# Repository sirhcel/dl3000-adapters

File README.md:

# Banana Jack and BNC Adapters for RIGOL DL3000 Electronic Loads

## Overview

This project is about banana jack and BNC adapters for RIGOL's DL3000 series
electronic loads. There are already adapters for narrower binding posts (like
BK Precision, ...) but I did not find any for the 39 mm pitch of the RIGOL
DL3000 series.

These adapters are meant for conveniently feeding a few amperes - not for high
current applications.

## Variants and Bills of Material

### BNC Adapter

The BNC adapter has a pretty standard footprint. So you should be able to find
a suitable replacement from your preferred distributor. Information on
replacement parts welcome.

* 1 PCB
    * KiCad design files form this repository
    * [Gerber and drill files](orders/dl3000-bnc-adapter-1.0-85dbc15.zip)
    * [Or just order it from OSH Park](https://oshpark.com/shared\_projects/MOcX6Gow)
* 1 [BNC connector](https://www.reichelt.de/steckverbinder-bnc-75-ohm-gerade-rnd-205-00437-p194660.html)

### Banana Jack Adapters

There are two board variants for sourcing the connectors from different
distributors.

#### PB4 Banana Jack Adapter

* 1 PCB
    * KiCad design files from this repository
    * [Gerber an drill files](orders/dl3000-banana-adapter-1.0-85dbc15.zip)
    * [Or just order it from OSH Park](https://oshpark.com/shared\_projects/gLsNtQ88)
* 1 connector Hirschmann Test and Measurement
  [PB4 red](https://www.reichelt.de/leiterplattenbuchse-4-mm-rot-pb-4-rt-p76865.html)
* 1 connector Hirschmann Test and Measurement
  [PB4 black](https://www.reichelt.de/leiterplattenbuchse-4-mm-schwarz-pb-4-sw-p13998.html)

#### 73099 Banana Jack Adapter

* 1 PCB
    * KiCad design files form this repository
    * [Gerber and drill files](orders/dl3000-banana-adapter-73099-1.1-8dd8051.zip)
    * [Or just order it from OSH Park](https://oshpark.com/shared_projects/TMnpJrJW)
* 1 connector Pomona [73099
  red](https://www.digikey.com/en/products/detail/pomona-electronics/73099-2/10483465)
* 1 connector Pomona [73099
  black](https://www.digikey.com/en/products/detail/pomona-electronics/73099-0/10483460)

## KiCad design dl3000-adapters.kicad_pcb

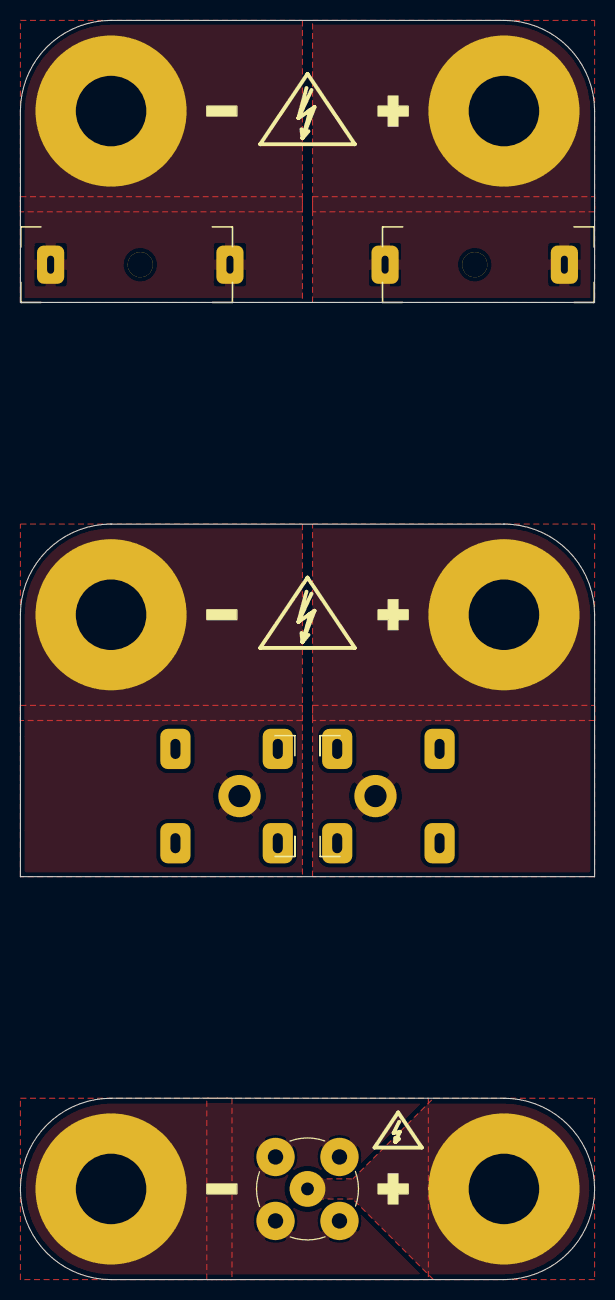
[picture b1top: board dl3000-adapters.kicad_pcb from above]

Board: 2 copper layers, 57.0 x 125.0 mm, 8 parts (0 on the bottom side), 6 nets, no tracks yet.

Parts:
J1, J3: Banana Jack; Hirschmann_SKS_PB4
J2: BNC; BNC_TEConnectivity_1478204_Vertical
J4, J5: Banana Jack; Pomona_73099
TP1, TP2, TP3: Binding Posts; TestPoint_2Pads_D15.0mm_Drill7.0mm_RIGOL_DL3000_Binding_Pos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

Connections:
/BANANA_73099+: J5.1, TP3.2
/BANANA_73099-: J4.1, TP3.1
/BANANA_PB4+: J3.1, TP1.2
/BANANA_PB4-: J1.1, TP1.1
/BNC+: J2.1, TP2.2
/BNC-: J2.2, TP2.1

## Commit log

2019-12-21 Add initial ignore rules
2019-12-21 Add initial schematic and footprints
2019-12-23 Rename to DL3000 Adapters
2019-12-23 Add first board layouts
2019-12-23 Add information on bottom silk screen
2019-12-23 Add comments to schematic and board
2019-12-23 Add high voltage symbols to top silk screen
    This includes deriving the very small and ultra small symbol from the
    copper layer variant already present in the library.
2019-12-23 Add data for ordering boards at OSH Park
2020-01-23 Add README.md with BOM
2020-01-23 Add license
2020-12-10 Combo per issue #1
2020-12-14 Bump silk screen version to 1.1
2020-12-14 Update order data and README
2020-12-14 Fix broken links of banana jack orders
2021-01-06 pomona footprint
2021-01-09 Fix position of lower left mounting PTH
2021-01-09 Add corner marks to silkscreen
2021-01-09 Use rectangular PTHs for mounting brackets
    These PTHs have some extra spacing in the vertical direction for
    allowing the connector pins to get inserted completely and the plastic
    case could sit right on top of the PCB. The rest rings got quite large
    allowing beefy solder joints to take the mechanical stress.
2021-01-09 Fix rest ring and mounting hole for PB4 footprint
2021-01-09 Add separate board for Pomona jacks
    It would be too much of a hassle to have both banana jack footprints
    overlap on the same board.
2021-01-09 Increase clearance on BNC board to 0.5 mm
    This adds some extra margin to the clearance of 0.4 mm I found on
    https://www.mikrocontroller.net/articles/Leiterbahnabst%C3%A4nde#Mindestkriechstrecken_bei_Leiterplatten
    for the input voltage rating of 150 V.
2021-04-23 Remove references from 73099 silk screen
2021-04-23 Add data for ordering 73099 board at OSH Park
2021-05-12 Update images and README.md for Pomona 73099
